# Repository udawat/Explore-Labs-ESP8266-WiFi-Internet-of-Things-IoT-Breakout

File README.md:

# Explore-Labs-ESP8266-WiFi-Internet-of-Things-IoT-Breakout
It is based on the widely popular ESP8266EX SoC from Espressif. It is breadboard friendly, supports input voltage from 3.3V to 5V and its level-shifted Tx, Rx pins are 5V compatible.

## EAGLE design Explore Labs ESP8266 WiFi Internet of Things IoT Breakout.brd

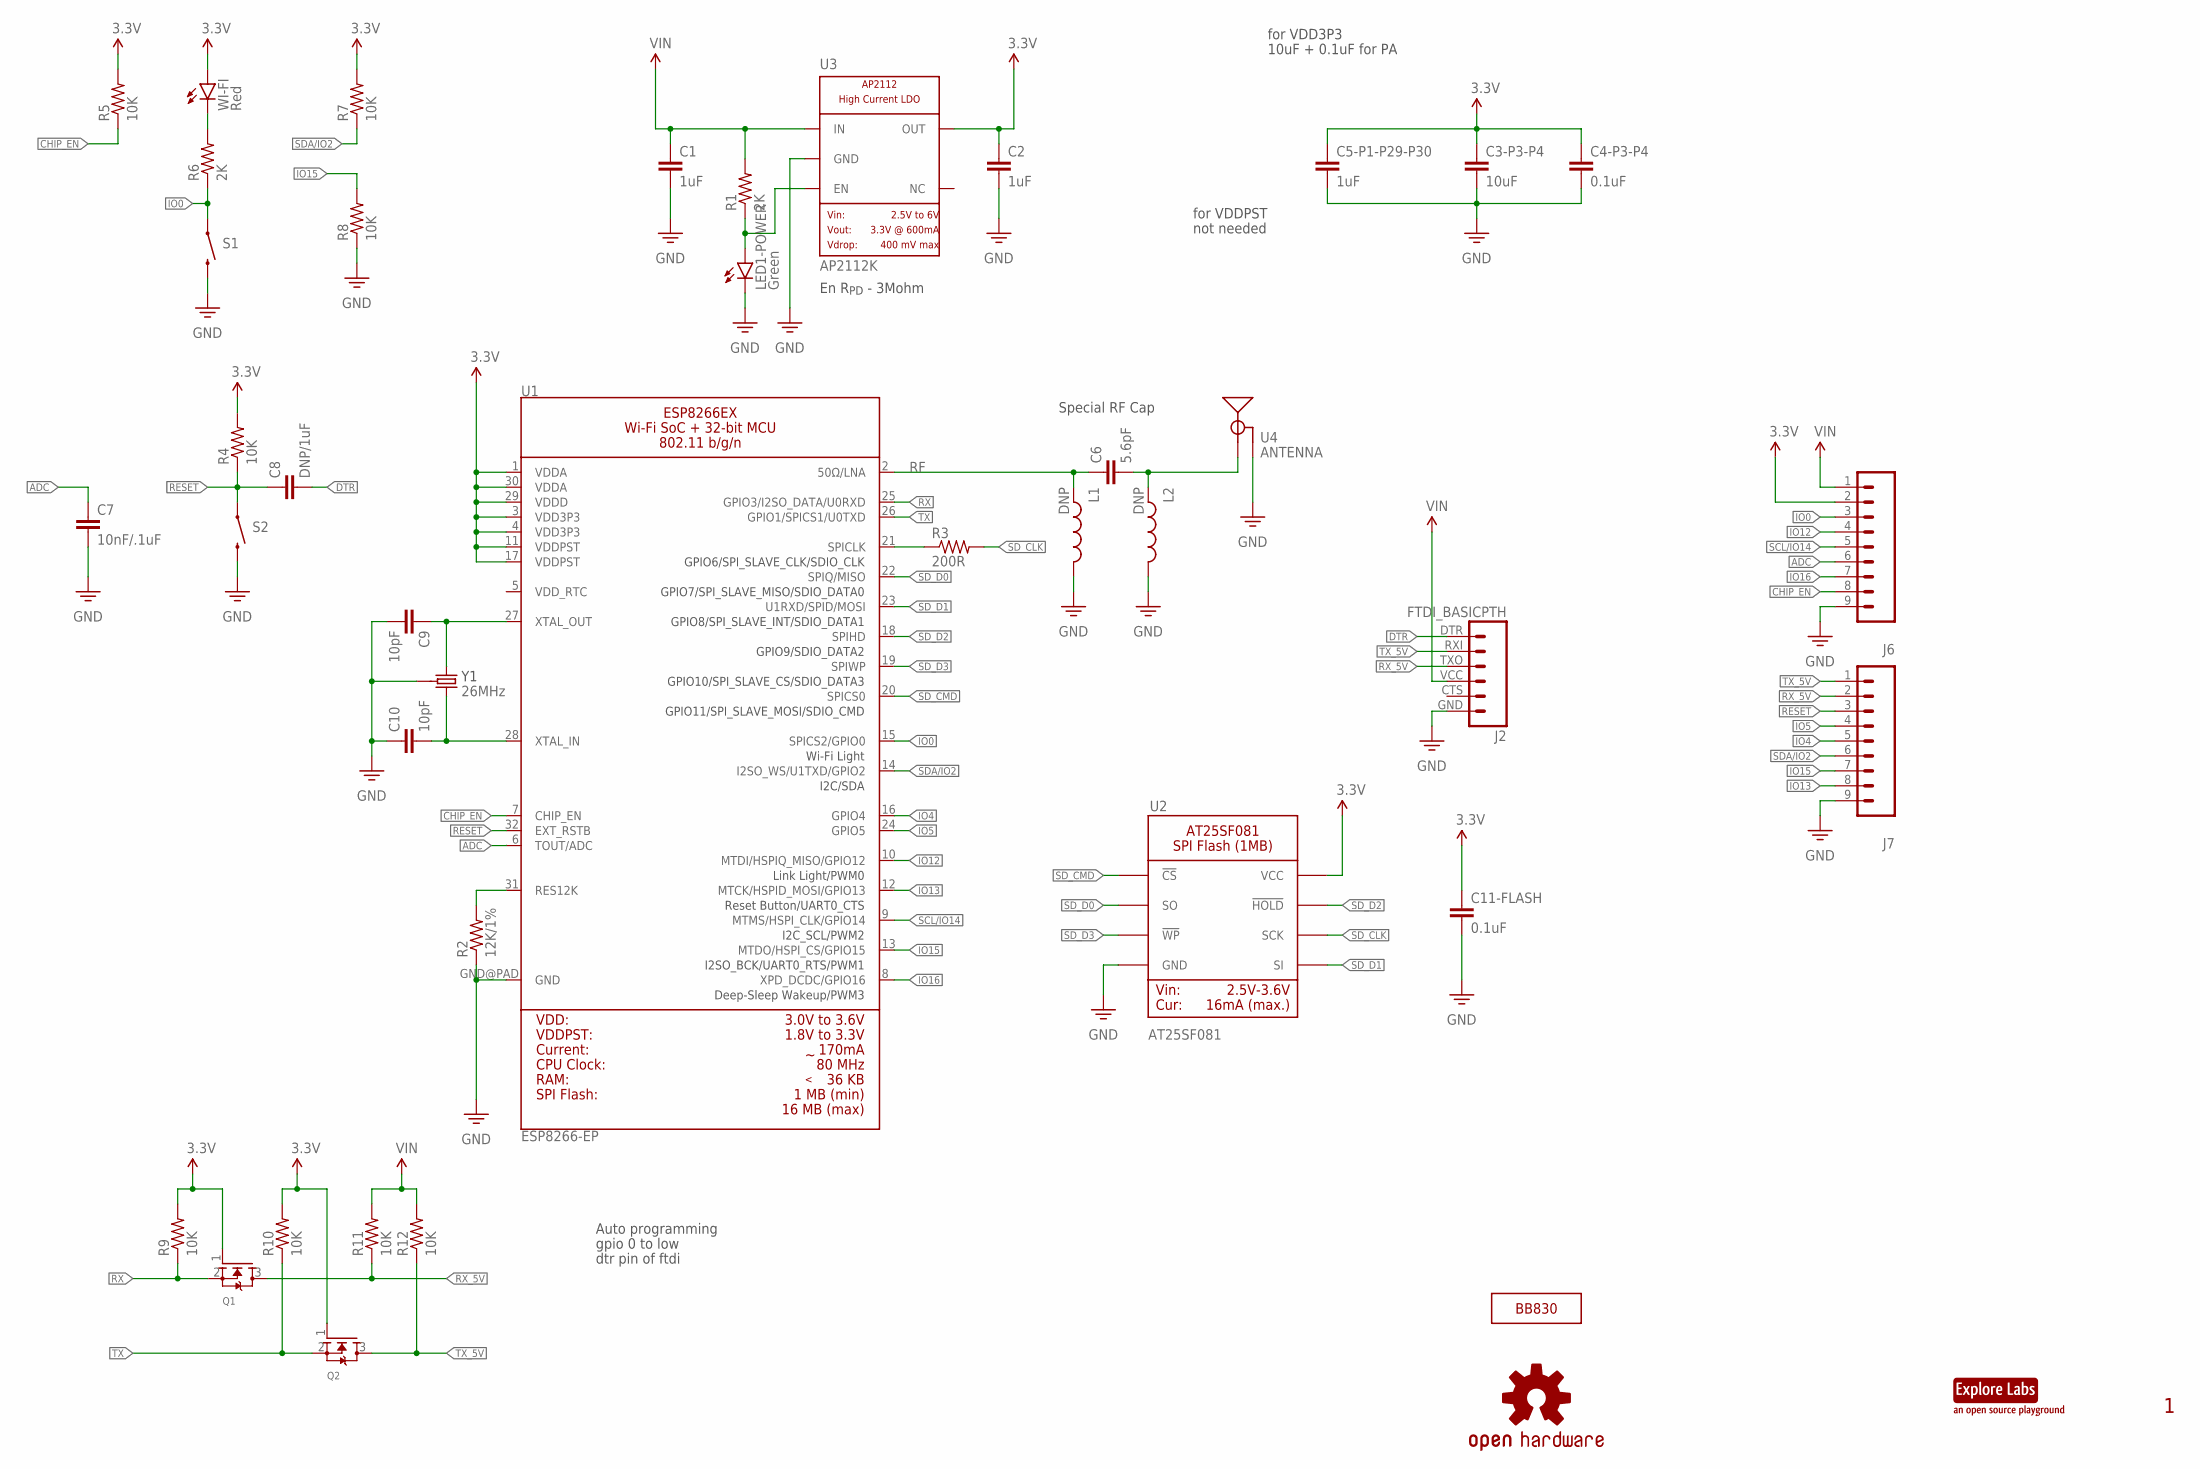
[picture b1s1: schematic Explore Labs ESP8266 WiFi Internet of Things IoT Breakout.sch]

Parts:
C1, C2, C5-P1-P29-P30: 1uF; 0402-CAP
C3-P3-P4: 10uF; 0603-CAP
C4-P3-P4, C11-FLASH: 0.1uF; 0402-CAP
C6: 5.6pF; 0402-CAP
C7: 10nF/.1uF; 0402-CAP
C8: DNP/1uF; 0402-CAP
C9, C10: 10pF; 0402-CAP
J2: FTDI_BASICPTH; FTDI_BASIC
J6, J7: M09; 1X09
L1, L2: DNP; 0402-FERRITE
LED1-POWER: Green; LED-0603
LOGO1: OSHW-LOGOBOTTOM; OSHW-LOGO-M-BOTTOM
Q1, Q2: MOSFET-N; SOT23
R1, R6: 2K; 0402-RES
R2: 12K/1%; 0402-RES
R3: 200R; 0402-RES
R4, R5, R7, R8, R9, R10, R11, R12: 10K; 0402-RES
S1, S2: SWITCH-NO-MOM; KXT-SWITCH
U1: ESP8266-EP; QFN32
U2: AT25SF081; SO08
U3: AP2112K; SOT23-LDO
U4: ANTENNA; ANTENNA-WROOM-02-INV
U$3: 26MHz; CRYSTAL-3225
U$4: EXPLORE-LABS-LOGOBOTTOM; EXLABS_LOGO_0.25
U$7: BREADBOARD-830
WI-FI: Red; LED-0603

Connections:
3.3V: C2.1, C3-P3-P4.1, C4-P3-P4.1, C5-P1-P29-P30.1, C11-FLASH.1, J6.2, Q1.1 (G), Q2.1 (G), R4.2, R5.2, R7.2, R9.2, R10.2, U1.1 (VDDA), U1.3 (VDD3P3), U1.4 (VDD3P3), U1.11 (VDDPST), U1.17 (VDDPST), U1.29 (VDDD), U1.30 (VDDA), U2.8 (VCC), U3.5 (OUT), WI-FI.A
ADC: C7.1, J6.6, U1.6 (TOUT/ADC)
CHIP_EN: J6.8, R5.1, U1.7 (CHIP_EN)
DTR: C8.2, J2.DTR (1)
GND: C1.2, C2.2, C3-P3-P4.2, C4-P3-P4.2, C5-P1-P29-P30.2, C7.2, C9.2, C10.1, C11-FLASH.2, J2.GND (6), J6.9, J7.9, L1.2, L2.2, LED1-POWER.C, R2.1, R8.1, S1.2, S2.2, U1.GND@PAD (GND), U2.4 (GND), U3.2 (GND), U4.GND, U$3.2 (3), U$3.4 (3)
IO0: J6.3, R6.1, S1.1, U1.15 (SPICS2/GPIO0)
IO4: J7.5, U1.16 (GPIO4)
IO5: J7.4, U1.24 (GPIO5)
IO12: J6.4, U1.10 (MTDI/HSPIQ_MISO/GPIO12)
IO13: J7.8, U1.12 (MTCK/HSPID_MOSI/GPIO13)
IO15: J7.7, R8.2, U1.13 (MTDO/HSPI_CS/GPIO15)
IO16: J6.7, U1.8 (XPD_DCDC/GPIO16)
unnamed: R3.1, U1.21 (SPICLK)
unnamed: R6.2, WI-FI.C
unnamed: LED1-POWER.A, R1.1, U3.3 (EN)
unnamed: C9.1, U1.27 (XTAL_OUT), U$3.1
unnamed: C10.2, U1.28 (XTAL_IN), U$3.3 (2)
unnamed: R2.2, U1.31 (RES12K)
unnamed: C6.2, L2.1, U4.SIG (SIGNAL)
RESET: C8.1, J7.3, R4.1, S2.1, U1.32 (EXT_RSTB)
RF: C6.1, L1.1, U1.2 (50Ω/LNA)
RX: Q1.2 (S), R9.1, U1.25 (GPIO3/I2SO_DATA/U0RXD)
RX_5V: J2.TXO (3), J7.2, Q1.3 (D), R11.1
SCL/IO14: J6.5, U1.9 (MTMS/HSPI_CLK/GPIO14)
SDA/IO2: J7.6, R7.1, U1.14 (I2SO_WS/U1TXD/GPIO2)
SD_CLK: R3.2, U2.6 (SCK)
SD_CMD: U1.20 (SPICS0), U2.1 (!CS)
SD_D0: U1.22 (SPIQ/MISO), U2.2 (SO)
SD_D1: U1.23 (U1RXD/SPID/MOSI), U2.5 (SI)
SD_D2: U1.18 (SPIHD), U2.7 (!HOLD)
SD_D3: U1.19 (SPIWP), U2.3 (!WP)
TX: Q2.2 (S), R10.1, U1.26 (GPIO1/SPICS1/U0TXD)
TX_5V: J2.RXI (2), J7.1, Q2.3 (D), R12.1
VIN: C1.1, J2.VCC (4), J6.1, R1.2, R11.2, R12.2, U3.1 (IN)

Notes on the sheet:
Auto programming
gpio 0 to low
dtr pin of ftdi
for VDD3P3
10uF + 0.1uF for PA
Special RF Cap
for VDDPST
not needed
En R_{PD} - 3Mohm

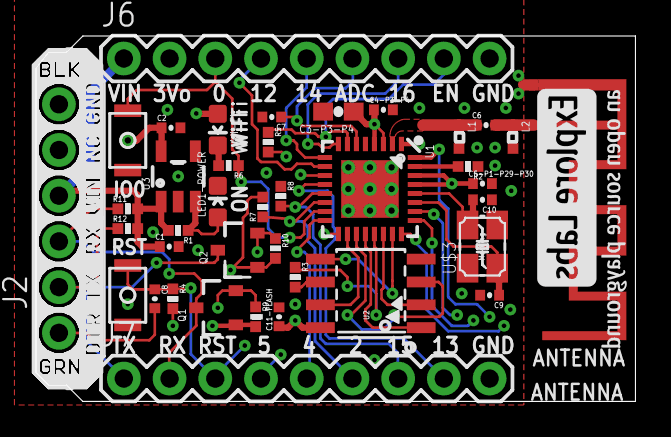
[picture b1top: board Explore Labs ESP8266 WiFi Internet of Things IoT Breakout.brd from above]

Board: 4 copper layers, 33.3 x 20.3 mm, 44 parts (1 on the bottom side), 34 nets.

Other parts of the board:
U$1: ESP-FTDI-BOTTOM
U$2: ESP-FTDI

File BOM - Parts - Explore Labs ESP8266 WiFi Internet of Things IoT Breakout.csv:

"Part";"Value";"Device";"Package";"Description";"";
"C1";"1uF";"CAPACITOR-0402";"0402-CAP";"";"";
"C2";"1uF";"CAPACITOR-0402";"0402-CAP";"";"";
"C3-P3-P4";"10uF";"CAPACITOR";"0603-CAP";"";"";
"C4-P3-P4";"0.1uF";"CAPACITOR-0402";"0402-CAP";"";"";
"C5-P1-P29-P30";"1uF";"CAPACITOR-0402";"0402-CAP";"";"";
"C6";"5.6pF";"CAPACITOR-0402";"0402-CAP";"";"";
"C7";"10nF/.1uF";"CAPACITOR-0402";"0402-CAP";"";"";
"C8";"DNP/1uF";"CAPACITOR-0402";"0402-CAP";"";"";
"C9";"10pF";"CAPACITOR-0402";"0402-CAP";"";"";
"C10";"10pF";"CAPACITOR-0402";"0402-CAP";"";"";
"C11-FLASH";"0.1uF";"CAPACITOR-0402";"0402-CAP";"";"";
"J2";"FTDI_BASICPTH";"FTDI_BASICPTH";"FTDI_BASIC";"FTDI Basic header with labels";"";
"J6";"";"M09";"1X09";"Header 9";"";
"J7";"";"M09";"1X09";"Header 9";"";
"L1";"DNP";"INDUCTOR";"0402-FERRITE";"Inductors";"";
"L2";"DNP";"INDUCTOR";"0402-FERRITE";"Inductors";"";
"LED1-POWER";"Green";"LED0603";"LED-0603";"LEDs";"";
"LOGO1";"OSHW-LOGOBOTTOM";"OSHW-LOGOBOTTOM";"OSHW-LOGO-M-BOTTOM";"Open Source Hardware Logo This logo indicates the piece of hardware it is found on incorporates a OSHW license and/or adheres to the definition of open source hardware found here: http://freedomdefined.org/OSHW";"";
"Q1";"";"MOSFET-N";"SOT23";"2N7002P";"";
"Q2";"";"MOSFET-N";"SOT23";"2N7002P";"";
"R1";"2K";"RESISTOR-0402";"0402-RES";"";"";
"R2";"12K/1%";"RESISTOR-0402";"0402-RES";"";"";
"R3";"200R";"RESISTOR-0402";"0402-RES";"";"";
"R4";"10K";"RESISTOR-0402";"0402-RES";"";"";
"R5";"10K";"RESISTOR-0402";"0402-RES";"";"";
"R6";"2K";"RESISTOR-0402";"0402-RES";"";"";
"R7";"10K";"RESISTOR-0402";"0402-RES";"";"";
"R8";"10K";"RESISTOR-0402";"0402-RES";"";"";
"R9";"10K";"RESISTOR-0402";"0402-RES";"";"";
"R10";"10K";"RESISTOR-0402";"0402-RES";"";"";
"R11";"10K";"RESISTOR-0402";"0402-RES";"";"";
"R12";"10K";"RESISTOR-0402";"0402-RES";"";"";
"S1";"SWITCH-NO-MOM";"SWITCH-NO-MOM";"KXT-SWITCH";"Normally Open switches - Pushbuttons (for reset), etc.";"";
"S2";"SWITCH-NO-MOM";"SWITCH-NO-MOM";"KXT-SWITCH";"Normally Open switches - Pushbuttons (for reset), etc.";"";
"U$3";"26MHz";"CRYSTAL-GROUNDED";"CRYSTAL-3225";"";"";
"U$4";"EXPLORE-LABS-LOGOBOTTOM";"EXPLORE-LABS-LOGOBOTTOM";"EXLABS_LOGO_0.25";"";"";
"U$7";"BREADBOARD-830";"BREADBOARD-830";"BREADBOARD-830";"";"";
"U1";"ESP8266-EP";"ESP8266-EP";"QFN32";"ESP8266EX";"";
"U2";"AT25SF081";"AT25SF081";"SO08";"AT25SF081";"";
"U3";"AP2112K";"AP2112K";"SOT23-LDO";"";"";
"U4";"ANTENNA";"ANTENNA";"ANTENNA-WROOM-02-INV";"2.4 GHz Inverted F Antenna";"";
"WI-FI";"Red";"LED0603";"LED-0603";"LEDs";"";

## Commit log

2016-04-19 added schematic and board design
    schematic in PDF and parts BOM in csv (; separated)

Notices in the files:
parts and their libraries:
SparkFun-LED: Licensing: Creative Commons ShareAlike 4.0 International - https://creativecommons.org/licenses/by-sa/4.0
Explore Labs EAGLE Library: Released under the Creative Commons
Explore Labs EAGLE Library: http://creativecommons.org/licenses/by-sa/4.0
